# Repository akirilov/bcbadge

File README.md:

# BCBadge

A project to create a business card that does something cool

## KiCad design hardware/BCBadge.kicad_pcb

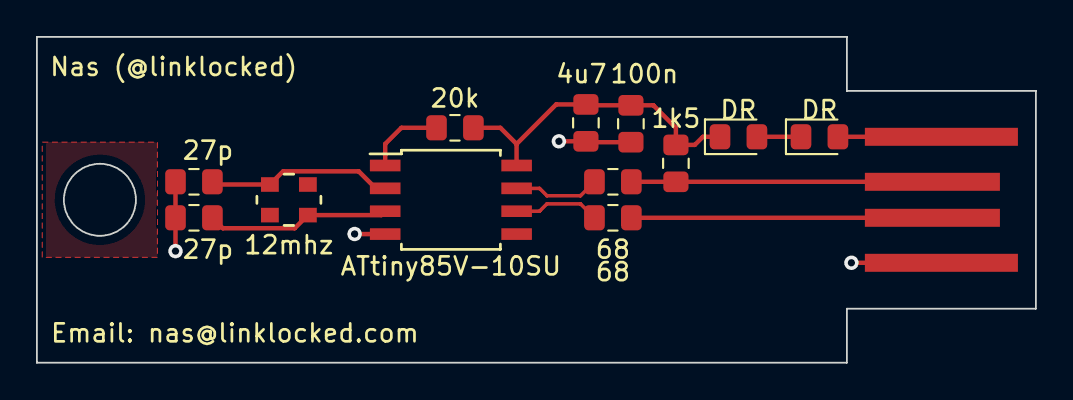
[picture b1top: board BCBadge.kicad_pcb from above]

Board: 2 copper layers, 55.5 x 18.1 mm, 13 parts (0 on the bottom side), 11 nets.

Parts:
C1: 100n; C_0805_2012Metric_Pad1.15x1.40mm_HandSolder
C2: 4u7; C_0805_2012Metric_Pad1.15x1.40mm_HandSolder
C3, C4: 27p; C_0805_2012Metric_Pad1.15x1.40mm_HandSolder
D1, D2: DR; D_0805_2012Metric_Pad1.15x1.40mm_HandSolder
R1: 20k; R_0805_2012Metric_Pad1.15x1.40mm_HandSolder
R2, R4: 68; R_0805_2012Metric_Pad1.15x1.40mm_HandSolder
R3: 1k5; R_0805_2012Metric_Pad1.15x1.40mm_HandSolder
U1: ATtiny85V-10SU; SOIJ-8_5.3x5.3mm_P1.27mm
U2: USB_A_Plug
Y1: 12mhz; ABM8G-12.000MHZ-B4Y-T3

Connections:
/USB_D+: R2.2, U1.6 (PB1)
/USB_D-: R4.2, U1.7 (PB2)
/XTAL_1: C3.2, U1.2 (XTAL1/PB3), Y1.1
/XTAL_2: C4.1, U1.3 (XTAL2/PB4), Y1.3
GND: C1.2, C2.2, C3.1, C4.2, U1.4 (GND), U2.4 (GND)
unnamed: D1.1 (K), D2.2 (A)
unnamed: D1.2 (A), U2.1 (VBUS)
unnamed: R1.2, U1.1 (~RESET~/PB5)
unnamed: R2.1, U2.3 (D+)
unnamed: R3.2, R4.1, U2.2 (D-)
VCC: C1.1, C2.1, D2.1 (K), R1.1, R3.1, U1.8 (VCC)

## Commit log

2020-04-17 v1 Card Badge
2020-04-17 Added README

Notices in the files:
parts and their libraries:
Copyright 2016 Accelerated Designs. All rights reserved.
